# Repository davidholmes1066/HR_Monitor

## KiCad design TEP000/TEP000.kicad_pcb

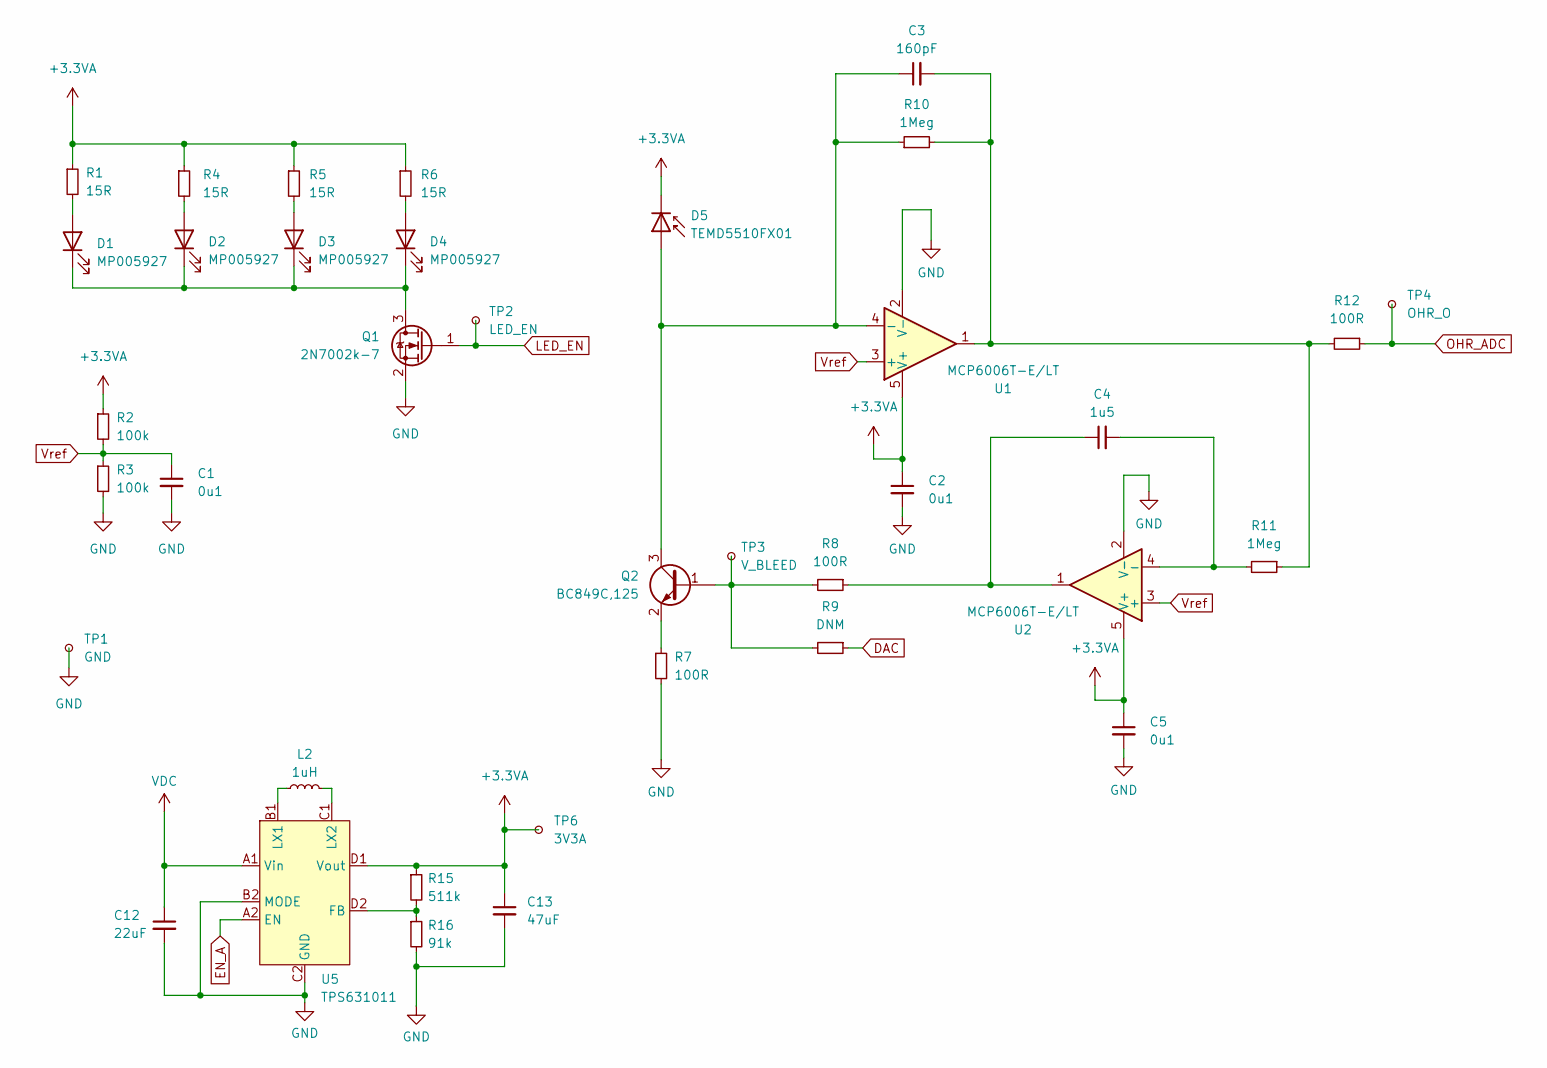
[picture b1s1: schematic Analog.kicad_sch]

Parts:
C1, C2, C5: 0u1; C_0402_1005Metric; Farnell 2627420
C3: 160pF; C_0402_1005Metric; Farnell 1758977
C4: 1u5; C_0603_1608Metric; Farnell 4066708
C12: 22uF; C_0805_2012Metric; Farnell 3013461
C13: 47uF; C_0805_2012Metric; Farnell 3582869
D1, D2, D3, D4: MP005927; D_0603_1608Metric
D5: TEMD5510FX01
L2: 1uH; L_0805_2012Metric_Pad1.05x1.20mm_HandSolder; Farnell 2616845
Q1: 2N7002k-7; SOT-23-3; Farnell 1713825
Q2: BC849C,125; SOT-23; Farnell 1081237
R1, R4, R5, R6: 15R; R_01005_0402Metric; Farnell 3994380
R2, R3: 100k; R_0402_1005Metric; Farnell 2502803
R7, R8, R12: 100R; R_0402_1005Metric; Farnell 2447095
R9: DNM; R_0402_1005Metric
R10, R11: 1Meg; R_0402_1005Metric; Farnell 2502805
R15: 511k; R_0402_1005Metric; Farnell 3950930
R16: 91k; R_0402_1005Metric; Farnell 2073314
TP1: GND; TestPoint_Pad_D1.0mm
TP2: LED_EN; TestPoint_Pad_D1.0mm
TP3: V_BLEED; TestPoint_Pad_D1.0mm
TP4: OHR_O; TestPoint_Pad_D1.0mm
TP6: 3V3A; TestPoint_Pad_D1.0mm
U1, U2: MCP6006T-E/LT; SOT-353_SC-70-5; Farnell 3807531
U5: TPS631011; Texas_DSBGA-8_0.705x1.468mm_Layout2x4_P0.4mm

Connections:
+3.3VA: C2.1, C5.1, C13.1, D5.1 (K), R1.1, R2.1, R4.1, R5.1, R6.1, R15.1, TP6.1, U1.5 (V+), U2.5 (V+), U5.D1 (Vout)
DAC: R9.1; also elsewhere on the board
EN_A: U5.A2 (EN); also elsewhere on the board
GND: C1.2, C2.2, C5.2, C12.2, C13.2, Q1.2 (S), R3.2, R7.2, R16.2, TP1.1, U1.2 (V-), U2.2 (V-), U5.B2 (MODE), U5.C2 (GND); also elsewhere on the board
LED_EN: Q1.1 (G), TP2.1; also elsewhere on the board
unnamed: C3.2, R10.2, R11.1, R12.2, U1.1
unnamed: C4.1, R8.1, U2.1
unnamed: D1.2 (A), R1.2
unnamed: D1.1 (K), D2.1 (K), D3.1 (K), D4.1 (K), Q1.3 (D)
unnamed: D2.2 (A), R4.2
unnamed: D3.2 (A), R5.2
unnamed: D4.2 (A), R6.2
unnamed: C3.1, D5.2 (A), Q2.3 (C), R10.1, U1.4 (-)
unnamed: Q2.1 (B), R8.2, R9.2, TP3.1
unnamed: Q2.2 (E), R7.1
unnamed: C4.2, R11.2, U2.4 (-)
unnamed: R15.2, R16.1, U5.D2 (FB)
unnamed: L2.1, U5.B1 (LX1)
unnamed: L2.2, U5.C1 (LX2)
OHR_ADC: R12.1, TP4.1; also elsewhere on the board
VDC: C12.1, U5.A1 (Vin); also elsewhere on the board
Vref: C1.1, R2.2, R3.1, U1.3 (+), U2.3 (+)

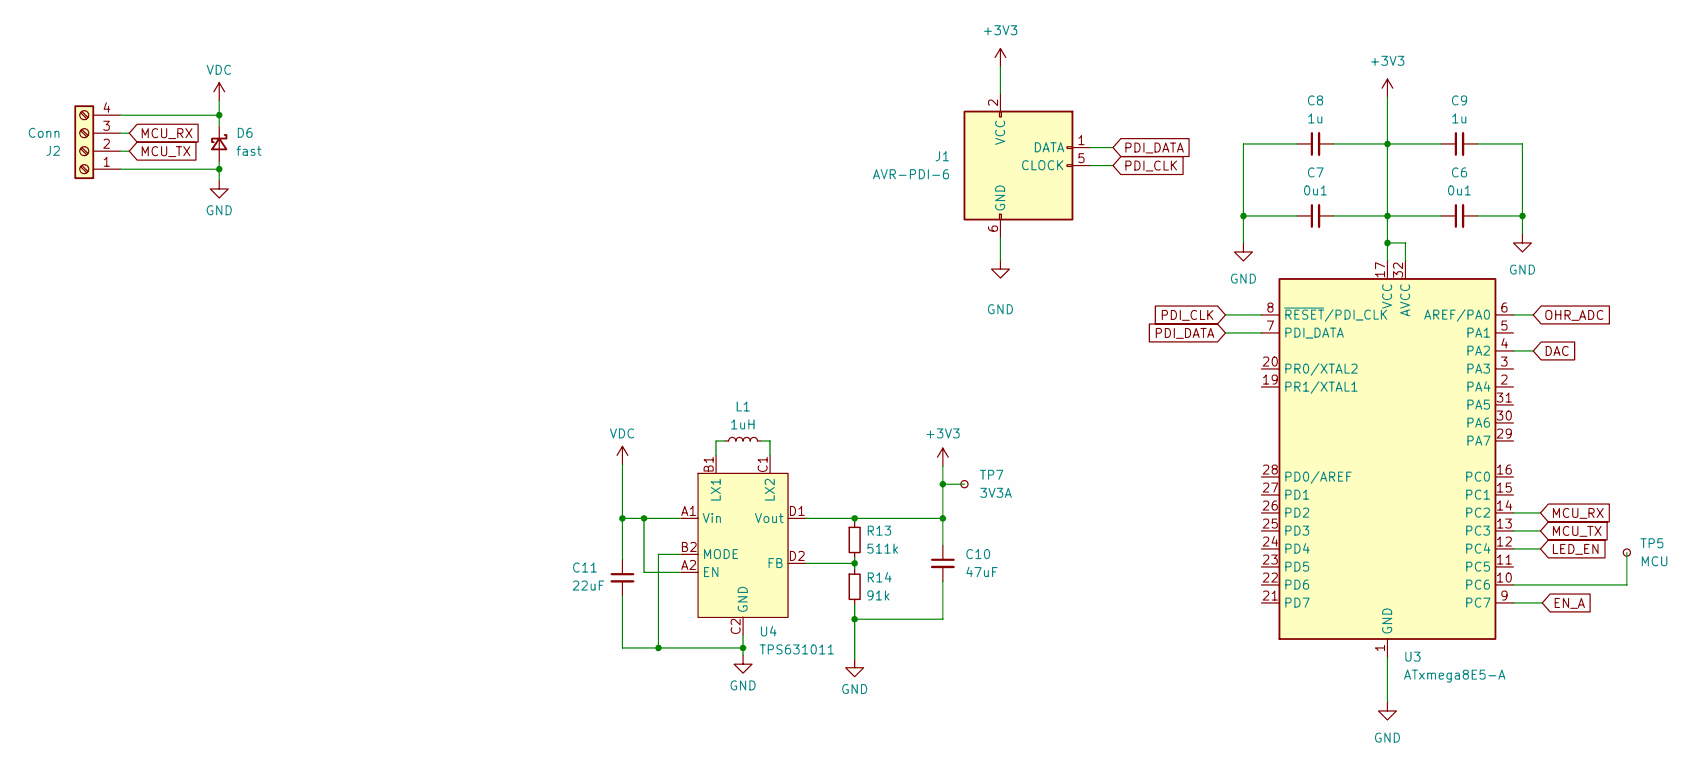
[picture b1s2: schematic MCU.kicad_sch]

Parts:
C6, C7: 0u1; C_0402_1005Metric; Farnell 2627420
C8, C9: 1u; C_0402_1005Metric; Farnell 3013330
C10: 47uF; C_0805_2012Metric; Farnell 3582869
C11: 22uF; C_0805_2012Metric; Farnell 3013461
D6: fast; D_SOD-128; Farnell 1829204
J1: AVR-PDI-6; PDI_AVR_TagConnect
J2: Conn; 3.81mm4PosTerm_2007987; Farnell 2007987
L1: 1uH; L_0805_2012Metric_Pad1.05x1.20mm_HandSolder; Farnell 2616845
R13: 511k; R_0402_1005Metric; Farnell 3950930
R14: 91k; R_0402_1005Metric; Farnell 2073314
TP5: MCU; TestPoint_Pad_D1.0mm
TP7: 3V3A; TestPoint_Pad_D1.0mm
U3: ATxmega8E5-A; TQFP-32_7x7mm_P0.8mm
U4: TPS631011; Texas_DSBGA-8_0.705x1.468mm_Layout2x4_P0.4mm

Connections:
3V3A_EN: U3.11 (PC5)
+3V3: C6.1, C7.2, C8.2, C9.1, C10.1, J1.2 (VCC), R13.1, TP7.1, U3.17 (VCC), U3.32 (AVCC), U4.D1 (Vout)
DAC: U3.4 (PA2); also elsewhere on the board
EN_A: U3.9 (PC7); also elsewhere on the board
GND: C6.2, C7.1, C8.1, C9.2, C10.2, C11.2, D6.2 (A), J1.6 (GND), J2.1, R14.2, U3.1 (GND), U3.18 (GND), U4.B2 (MODE), U4.C2 (GND); also elsewhere on the board
LED_EN: U3.12 (PC4); also elsewhere on the board
MCU_RX: J2.3, U3.14 (PC2)
MCU_TX: J2.2, U3.13 (PC3)
unnamed: TP5.1, U3.10 (PC6)
unnamed: L1.1, U4.B1 (LX1)
unnamed: R13.2, R14.1, U4.D2 (FB)
unnamed: L1.2, U4.C1 (LX2)
OHR_ADC: U3.6 (AREF/PA0); also elsewhere on the board
PDI_CLK: J1.5 (CLOCK), U3.8 (~RESET/PDI_CLK)
PDI_DATA: J1.1 (DATA), U3.7 (PDI_DATA)
VDC: C11.1, D6.1 (K), J2.4, U4.A1 (Vin), U4.A2 (EN); also elsewhere on the board

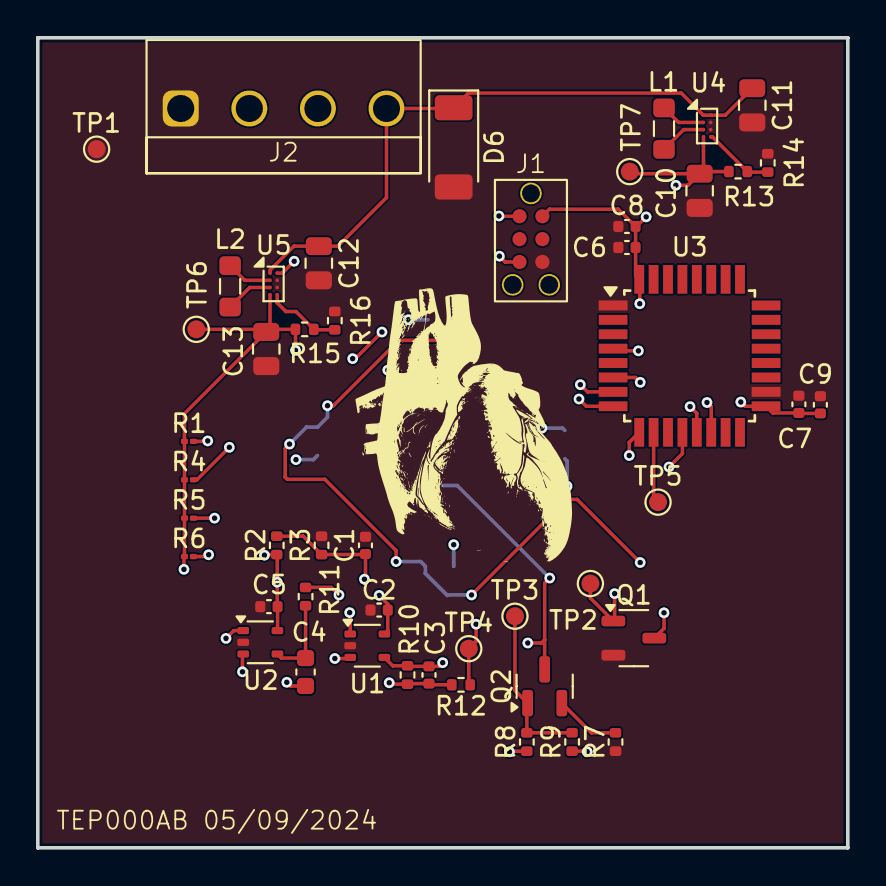
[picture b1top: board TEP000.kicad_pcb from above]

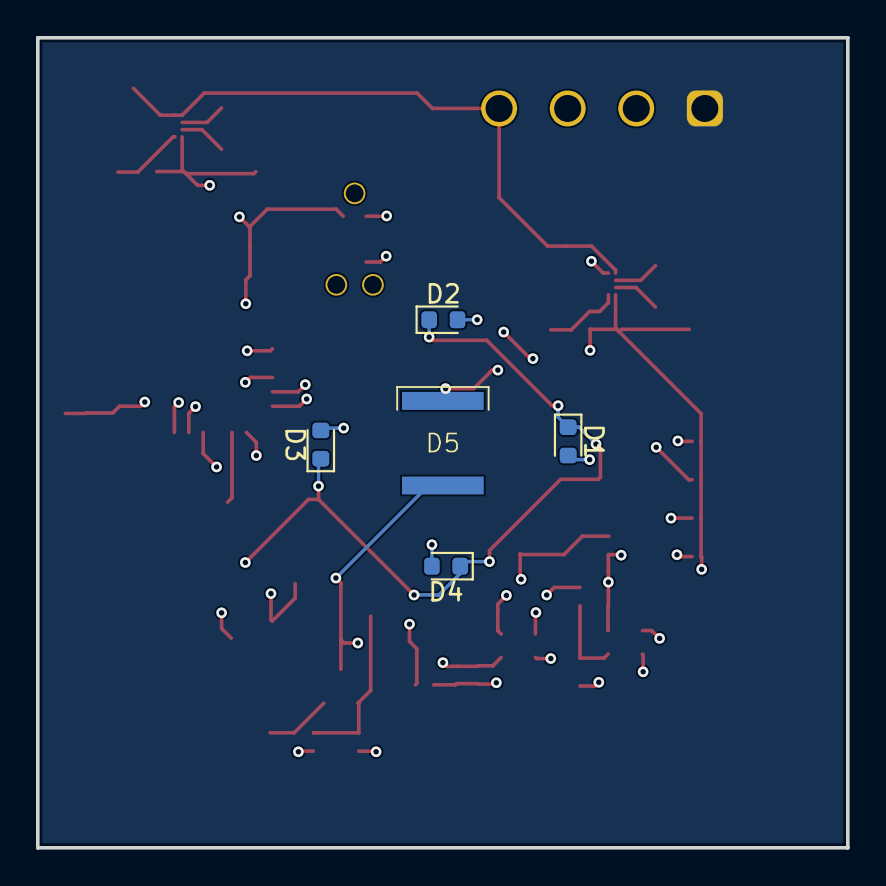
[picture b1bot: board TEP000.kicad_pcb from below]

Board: 4 copper layers, 45.0 x 45.0 mm, 53 parts (5 on the bottom side), 31 nets.

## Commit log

2024-08-03 added LED and Photodiodes
2024-08-06 added transimpedance amplifier
2024-08-09 First rev of TEP000 Prototype
2024-08-28 TEP000AA
    Device works but now way of filtering out the DC offset current saturating the amplifier. Should be made cheaper and possibly with a single supply. Will add an MCU so that a first revision of the fir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
2024-08-28 Started work on rev AB
2024-09-05 TEP000AB
    Added buck-boost converters, MCU and integrator bleed circuit.
